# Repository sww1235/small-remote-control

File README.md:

# small-remote-control
 a small remote control designed to be mounted on the end of a wire. Has variation with built in resistors for android media control.

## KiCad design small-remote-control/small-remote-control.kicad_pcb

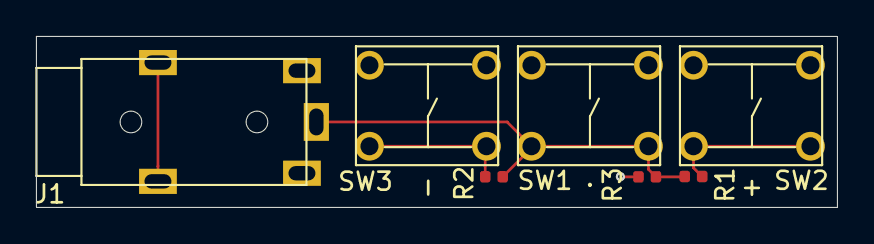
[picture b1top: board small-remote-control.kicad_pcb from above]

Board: 2 copper layers, 44.5 x 9.5 mm, 7 parts (0 on the bottom side), 4 nets.

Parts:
J1: AudioJack4; 54-00174
R1: 267Ω ±0.1%; R_0402_1005Metric
R2: 604Ω ±0.1%; R_0402_1005Metric
R3: 2k21Ω ±0.1%; R_0402_1005Metric
SW1: A; B3W-6x6mm-NG
SW2: B; B3W-6x6mm-NG
SW3: C; B3W-6x6mm-NG

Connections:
/GND: J1.R2, R3.1, SW1.2, SW2.2, SW3.2
/MIC: J1.S, R1.2, R2.2, R3.2, SW1.1
unnamed: R1.1, SW2.1
unnamed: R2.1, SW3.1

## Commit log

2020-08-01 Starting project
2020-08-02 Started PCB
2020-08-02 removed feedthrough jack and moved switches closer
2020-08-02 removed mic and switch D, added 2.2kΩ resistor
2020-08-11 switched to 0603 resistors
2020-08-29 moved around fab layer for easier visibility
